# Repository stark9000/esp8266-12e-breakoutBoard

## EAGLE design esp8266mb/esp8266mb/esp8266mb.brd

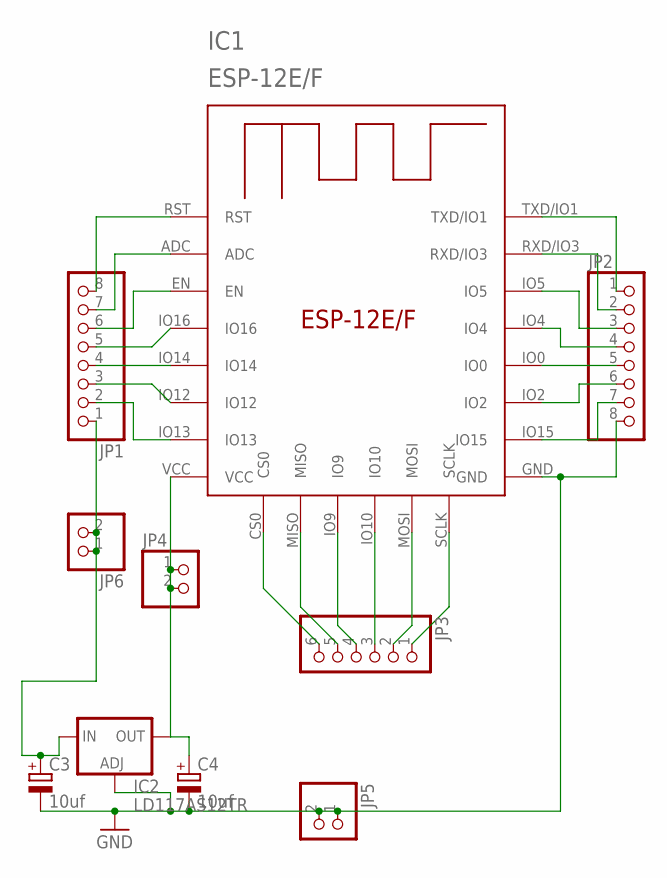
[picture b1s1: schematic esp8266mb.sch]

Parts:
C3, C4: 10uf; E5-5
IC1: ESP-12E/F; ESP-12E
IC2: LD117AS12TR; SOT223
JP1, JP2: PINHD-1X8; 1X08
JP3: PINHD-1X6; 1X06
JP4, JP5, JP6: PINHD-1X2; 1X02

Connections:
GND: C3.-, C4.-, IC1.GND, IC2.1 (ADJ), JP2.8, JP5.1, JP5.2
unnamed: IC1.RST, JP1.8
unnamed: IC1.ADC, JP1.7
unnamed: IC1.EN, JP1.6
unnamed: IC1.IO16, JP1.5
unnamed: IC1.IO14, JP1.4
unnamed: IC1.IO12, JP1.3
unnamed: IC1.IO13, JP1.2
unnamed: C3.+, IC2.3 (IN), JP1.1, JP6.1, JP6.2
unnamed: IC1.TXD/IO1, JP2.1
unnamed: IC1.RXD/IO3, JP2.2
unnamed: IC1.IO5, JP2.3
unnamed: IC1.IO15, JP2.7
unnamed: IC1.IO2, JP2.6
unnamed: IC1.IO0, JP2.5
unnamed: IC1.IO4, JP2.4
unnamed: IC1.CS0, JP3.6
unnamed: IC1.SCLK, JP3.1
unnamed: IC1.MOSI, JP3.2
unnamed: IC1.MISO, JP3.5
unnamed: IC1.IO9, JP3.4
unnamed: IC1.IO10, JP3.3
unnamed: C4.+, IC1.VCC, IC2.4 (OUT), JP4.1, JP4.2

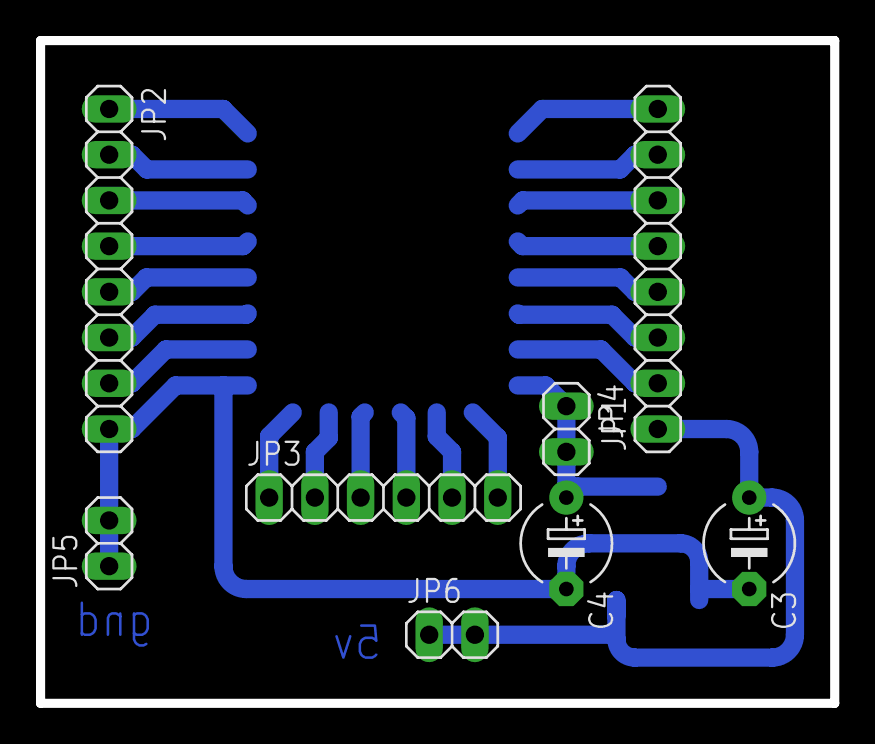
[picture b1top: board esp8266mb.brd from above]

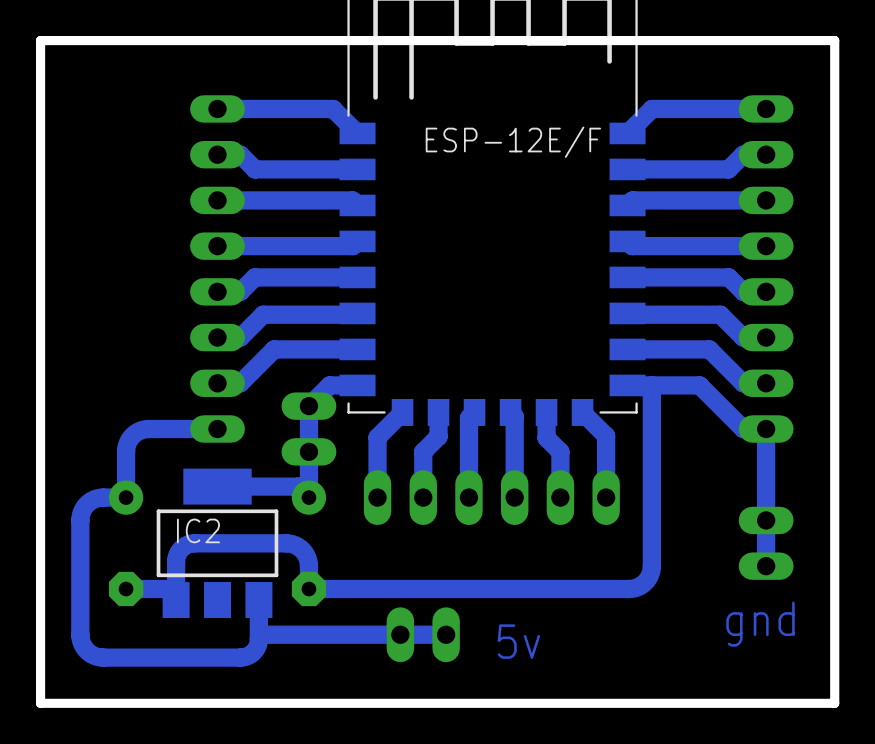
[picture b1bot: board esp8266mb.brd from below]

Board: 2 copper layers, 44.1 x 36.8 mm, 10 parts (2 on the bottom side), 23 nets.
